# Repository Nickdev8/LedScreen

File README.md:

# Led Control Board
Status: PCB, Firmware, Hardware and examples are Completly done!

With this board you can control multiple WS2812 LED lines with XLight sequences.
The main idea is that I wanted one board that could handle the panel data, SD card playback, and animation syncing between boards. That i all achieved with this pcb.

## Project Purpose
### Why I Built This
One of my close friends, Ruben, wanted to build a big LED panel project with me so we could display text, animations, and more.
After this board is fully working, I also want to use it in 2 daft punk helmets for Comic-Con 2026.

### BOM
- Raspberry Pi Pico
- 74HCT245
- 1000uF Cap
- 8x 220 ohm Resistor
- 100nF Cap (optionaly)
- 4.7uF Cap (optionaly)
- 2x 10k Res (optionaly for board Sync)

## How do you use it?
If you want to update the code on the MCU, I would really suggest reading [The firmware instuctions](docs/FIRMWARE_INSTUCTIONS.md).
If you want to update the animations on the display, read [the animation instuctions](docs/ANIMATIONS_INSTUCTIONS.md).

The basic idea is:
1. Flash the Pico with the firmware from `arduino_firmware/Main/`.
2. Put `.lsa` animation files in the SD card root.
3. Connect the LED panels and power them from an external regulated 5V PSU.
4. If needed, chain multiple boards together with the sync in/out headers.

## Firmware / Software
The Pico runs my own firmware in the [`arduino_firmware/`](arduino_firmware/) folder.
To Install make sure you have the `Earle Philhower Arduino-Pico core board` library

### SD Card Playback
- The Pico firmware reads root-level `.lsa` files from a FAT32 SD card.
- Files named `startup*.lsa` play once at boot in case-insensitive alphabetical order.
- Every other `.lsa` file then plays in case-insensitive alphabetical order, repeating the complete playlist forever.
- Prefix normal files with numbers such as `01_intro.lsa` and `02_logo.lsa` to control their order.
- Long filenames such as `startup_1.lsa` are supported.
- USB live streaming and GIF playback are not part of the active firmware.

## Project Files
- [`pcb/src/`](pcb/src/LedScreen.kicad_sch) - PCB sourse
- [`pcb/exports/LedScreen.pdf`](pcb/exports/LedScreen.pdf) - exported schematic PDF
- [`pcb/exports/gerber.zip`](pcb/exports/gerber.zip) - gerbers bundled for fabrication upload
- [`pcb/Gerber/`](pcb/Gerber/) - individual gerber outputs
- [`pcb/bom/ibom.html`](pcb/bom/ibom.html) - interactive BOM
- [`mechanical/case/`](mechanical/case/) - case and standoff print files
- [`xlights_project/`](xlights_project/) - xLights example project for driving the board
- [`scripts/fseq_to_lsa.py`](scripts/fseq_to_lsa.py) - convert xLights FSEQ files to `.lsa`

## Notes
I also included an xLights example for controlling this board.
xLights configuration depends on the final data path used between xLights and the Pico.

Start with a smaller amount of daisy-chained panels per output lane while validating signal integrity and power behavior.
Use an external 5V PSU sized for the actual panel count and brightness.

## Bill of Materials
Interactive BOM: [cdn.nickesselman.nl](https://cdn.nickesselman.nl/ledpanel/ibom.html)

## Project Images

## Build Photos

## License
- Hardware: CERN-OHL-S
- Firmware/Software: MIT License
- 

# Daft Punk Helmets
I used this project for 2 Helmets, Guy manual (gold) & Thomas (Silver)
all 3d printed in about 200h of print time. and LED strips on the inside for the classic robot screen.
Models are in the repo and how i made this you can google and find on instrucables

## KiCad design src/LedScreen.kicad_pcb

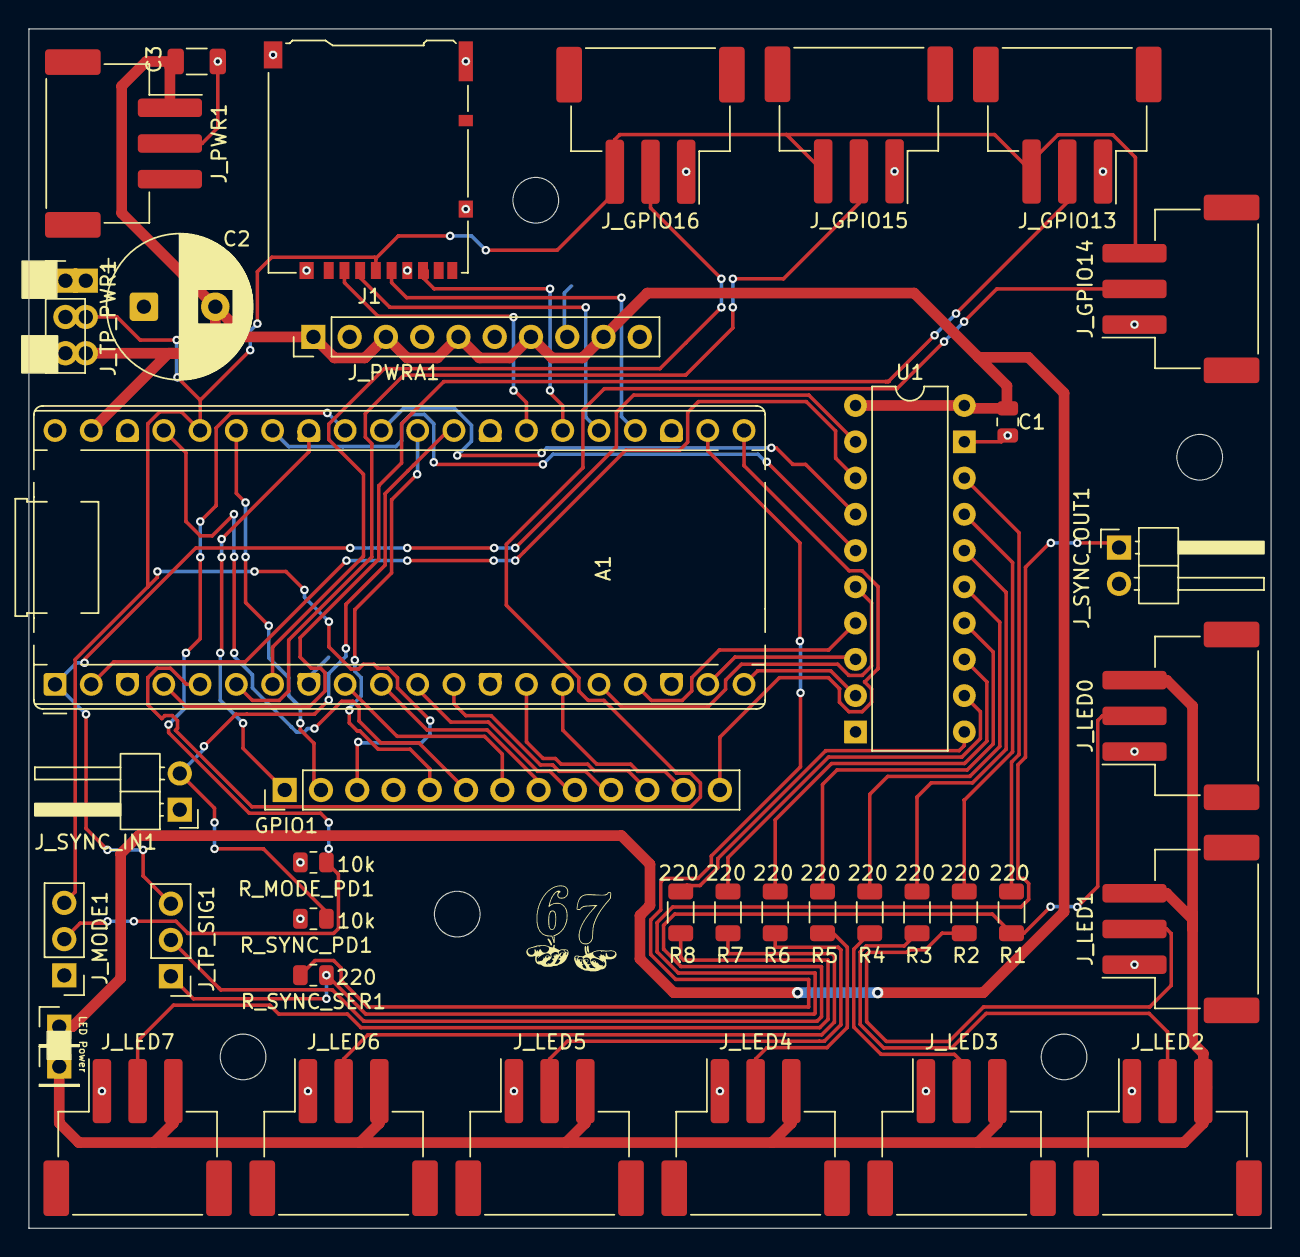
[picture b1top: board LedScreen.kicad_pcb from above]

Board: 2 copper layers, 87.0 x 84.0 mm, 39 parts (0 on the bottom side), 51 nets.

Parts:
A1: RaspberryPi_Pico; RaspberryPi_Pico_Common_THT
C1: 100nF; C_0805_2012Metric
C2: 1000uF; CP_Radial_D10.0mm_P5.00mm
C3: 4.7uF; C_1206_3216Metric
GPIO1: Conn_01x13; PinHeader_1x13_P2.54mm_Vertical
J1: Micro_SD_Card_Det_Hirose_DM3AT; microSD_HC_Hirose_DM3AT-SF-PEJM5
J_GPIO13: SPARE_GPIO_13; JST_XH_S3B-XH-SM4-TB_1x03-1MP_P2.50mm_Horizontal
J_GPIO14: SPARE_GPIO_14; JST_XH_S3B-XH-SM4-TB_1x03-1MP_P2.50mm_Horizontal
J_GPIO15: SPARE_GPIO_15; JST_XH_S3B-XH-SM4-TB_1x03-1MP_P2.50mm_Horizontal
J_GPIO16: SPARE_GPIO_16; JST_XH_S3B-XH-SM4-TB_1x03-1MP_P2.50mm_Horizontal
J_LED0, J_LED1, J_LED2, J_LED3, J_LED4, J_LED5, J_LED6, J_LED7: Conn_01x03; JST_XH_S3B-XH-SM4-TB_1x03-1MP_P2.50mm_Horizontal
J_MODE1: Conn_01x03; PinHeader_1x03_P2.54mm_Vertical
J_PWR1: Conn_01x03; JST_XH_S3B-XH-SM4-TB_1x03-1MP_P2.50mm_Horizontal
J_PWRA1: Conn_01x10; PinHeader_1x10_P2.54mm_Vertical
J_SYNC_IN1: Conn_01x02; PinHeader_1x02_P2.54mm_Horizontal
J_SYNC_OUT1: Conn_01x02; PinHeader_1x02_P2.54mm_Horizontal
J_TP_PWR1: TP_PWR; PinHeader_1x03_P2.54mm_Vertical
J_TP_SIG1: TP_SIG; PinHeader_1x03_P2.54mm_Vertical
R1, R2, R3, R4, R5, R6, R7, R8: 220; R_1206_3216Metric
R_MODE_PD1: 10k; R_0805_2012Metric
R_SYNC_PD1: 10k; R_0805_2012Metric
R_SYNC_SER1: 220; R_0805_2012Metric
U1: 74HCT245; DIP-20_W7.62mm
V2, V5: Conn_01x01_Pin; PinHeader_1x01_P2.54mm_Vertical

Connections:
3V3_EN: A1.37 (3V3_EN), GPIO1.6
+3V3: A1.36 (3V3), GPIO1.3, J1.4 (VDD), J_GPIO13.3, J_GPIO14.3, J_GPIO15.3, J_GPIO16.3, J_MODE1.3, J_TP_PWR1.2
+5V: A1.39 (VSYS), C1.1, C2.2, C3.2, J_PWR1.1, J_PWRA1.1, J_PWRA1.3, J_PWRA1.5, J_PWRA1.7, J_PWRA1.9, J_TP_PWR1.3, U1.1 (A->B), U1.20 (VCC), V2.1
ADC_VREF: A1.35 (ADC_VREF), GPIO1.2
AGND: A1.33 (AGND), GPIO1.1
GND: A1.3 (GND), A1.8 (GND), A1.13 (GND), A1.18 (GND), A1.23 (GND), A1.28 (GND), A1.38 (GND), C1.2, C2.1, C3.1, GPIO1.4, J1.6 (VSS), J1.11 (SHIELD), J_GPIO13.1, J_GPIO14.1, J_GPIO15.1, J_GPIO16.1, J_LED0.1, J_LED1.1, J_LED2.1, J_LED3.1, J_LED4.1, J_LED5.1, J_LED6.1, J_LED7.1, J_MODE1.1, J_PWR1.2, J_PWRA1.2, J_PWRA1.4, J_PWRA1.6, J_PWRA1.8, J_PWRA1.10, J_SYNC_IN1.1, J_SYNC_OUT1.2, J_TP_PWR1.1, R_MODE_PD1.1, R_SYNC_PD1.1, U1.10 (GND), U1.19 (CE)
GPIO2: A1.4 (GPIO2), J_GPIO13.2
GPIO3: A1.5 (GPIO3), J_GPIO14.2
GPIO4: A1.6 (GPIO4), J_GPIO15.2
GPIO5: A1.7 (GPIO5), J_GPIO16.2
GPIO6: A1.9 (GPIO6), GPIO1.7
GPIO7: A1.10 (GPIO7), GPIO1.8
GPIO8: A1.11 (GPIO8), GPIO1.9
GPIO9: A1.12 (GPIO9), GPIO1.10
GPIO10: A1.14 (GPIO10), GPIO1.11
GPIO11: A1.15 (GPIO11), GPIO1.12
GPIO16: A1.21 (GPIO16), GPIO1.13
LED0_DATA: J_LED0.2, J_TP_SIG1.2, R1.2
LED1_DATA: J_LED1.2, R2.2
LED2_DATA: J_LED2.2, R3.2
LED3_DATA: J_LED3.2, R4.2
LED4_DATA: J_LED4.2, R5.2
LED5_DATA: J_LED5.2, R6.2
LED6_DATA: J_LED6.2, R7.2
LED7_DATA: J_LED7.2, R8.2
LED_PIN3: J_LED0.3, J_LED1.3, J_LED2.3, J_LED3.3, J_LED4.3, J_LED5.3, J_LED6.3, J_LED7.3, V5.1
MODE: A1.32 (GPIO27_ADC1), J_MODE1.2, R_MODE_PD1.2
unnamed: R1.1, U1.18 (B0)
unnamed: R2.1, U1.17 (B1)
unnamed: R3.1, U1.16 (B2)
unnamed: R4.1, U1.15 (B3)
unnamed: R5.1, U1.14 (B4)
unnamed: R6.1, U1.13 (B5)
unnamed: R7.1, U1.12 (B6)
unnamed: R8.1, U1.11 (B7)
RUN: A1.30 (RUN), GPIO1.5
SD_CS: A1.27 (GPIO21), J1.2 (DAT3/CD)
SD_MISO: A1.26 (GPIO20), J1.7 (DAT0)
SD_MOSI: A1.25 (GPIO19), J1.3 (CMD)
SD_SCK: A1.24 (GPIO18), J1.5 (CLK)
SYNC_IN: A1.29 (GPIO22), J_SYNC_IN1.2, R_SYNC_PD1.2
SYNC_OUT: J_SYNC_OUT1.1, J_TP_SIG1.1, R_SYNC_SER1.2
SYNC_OUT_DRV: A1.22 (GPIO17), R_SYNC_SER1.1
T_OUT0: A1.1 (GPIO0), J_TP_SIG1.3, U1.2 (A0)
T_OUT1: A1.2 (GPIO1), U1.3 (A1)
T_OUT2: A1.31 (GPIO26_ADC0), U1.4 (A2)
T_OUT3: A1.34 (GPIO28_ADC2), U1.5 (A3)
T_OUT4: A1.16 (GPIO12), U1.6 (A4)
T_OUT5: A1.17 (GPIO13), U1.7 (A5)
T_OUT6: A1.19 (GPIO14), U1.8 (A6)
T_OUT7: A1.20 (GPIO15), U1.9 (A7)

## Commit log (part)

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2026-02-27 added caps to 5v + gnd
2026-03-01 DONE WIRINg
2026-03-01 chore: checkpoint before reroute
2026-03-02 removed all tracks
2026-03-03 finsighed new v2 routing
2026-03-03 updated gitignore
2026-03-03 Reorganize KiCad project layout
2026-03-03 Update Teensy library submodule refs
2026-03-03 Add firmware and lighting project artifacts
2026-03-03 Add MIT License to the project
2026-03-03 added Bom+Journal
2026-03-04 ITWIRJS
2026-03-04 FIRMWARE DONEE!
2026-03-07 Add project link to README
    Added project link to the README.
2026-03-07 Update image display in README.md
    Removed table layout for images and added individual image tags with reduced width.
2026-03-07 Updare README
2026-03-09 FINAL BLOWW! added gerbers added new images, uploaded carts
2026-03-09 updated raedme
2026-03-09 bakced up adrinoo firmware
2026-03-09 Worked on SD card Aninmation loading
2026-03-17 made .blend standoff files
2026-03-18 updated models for more Stiffness
2026-03-22 Add image of PCB to README
2026-04-01 updated power injection wireing
2026-04-14 AGAGAHAGAHAGHAGAH op schoool
2026-04-17 Fix spelling errors and update project status
    Corrected spelling errors and updated project status.
2026-04-17 update readme!!
2026-04-18 Add Main firmware, SDREADD, fseq converter; clean up AI/build artifacts
    - arduino_firmware/Main/: new combined firmware
    - Sd.cpp/h: bare-metal SPI SD driver + FAT32 + LSA streaming
    - Leds.cpp/h: 8-lane NeoPixel, pixel mapping, idle blink, current limit
    - UsbStream.cpp/h: xLights USB serial streaming with frame sync
    - Main.ino: setup + loop only
    - Config.h: 20-panel (160×32) layout, safety limits at top
2026-04-19 Switch to Adafruit NeoPXL8 for true parallel 8-lane output
    Replaces 8 separate NeoPixel show() calls (sequential, ~154ms, ~6.5fps max)
    with a single NeoPXL8 show() via RP2040 PIO+DMA — all lanes fire simultaneously
    (~23ms for longest lane → ~43fps max). Fixes panel sync drift.
    Also: pin order corrected (lanes 0-3 → GPIOs 12-15 physical top row, lanes 4-7
    → GPIOs 0,1,26,28 physical bottom), orphaned serial stream stubs removed from
    Leds.cpp, xlights project and animation.lsa updated.
2026-04-19 switched to a adafruit library and got 43fps working
2026-04-19 Clean up the repository structure so project assets are easier to find
    The project had accumulated PCB exports, mechanical files, screenshots,
    examples, and helper scripts at the repo root. Group related artifacts
    under docs/, pcb/, mechanical/, examples/, and scripts/ so the root stays
    readable and common assets are easier to locate.
    Constraint: Preserve existing project contents while reorganizing tracked assets
    Constraint: Keep the example UF2 tracked after moving it under examples/
2026-04-19 Add build photos to the README so the hardware state is easier to see
    The repository already had renders and fabrication screenshots, but it was
    missing clear photos of the assembled controller and panel test setup. Add
    both images under docs/images/ and link them from the README.
    Constraint: Keep the photos inside the existing docs image structure
    Confidence: high
    Scope-risk: narrow
2026-04-19 updated images in readme
2026-04-29 BAGHBAHGAGVAHABGHAAA
2026-04-29 lamp fully working all panel corrections +gif and mp4 script start implementing
2026-05-23 added examples, added code for single strips. updated readme. and added BEE MOVIE!
2026-05-23 added zine
2026-05-23 updated zine
2026-05-23 added BOMs
2026-06-17 removed legacy usb live, and gif support
2026-06-18 added the daftpunk helmets models
